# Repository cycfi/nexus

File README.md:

# Nexus
The Nexus is a small, flexible, and hacker friendly breakout box that connects your multichannel guitar to the outside world using a specialized (LEMO compatible) multi-pin connector for up to 15 channels of audio and 7 channels of analog control voltages for by-wire (remote) control of volume, tone, patch or effects. Audio may come from standard mono-pickups or from the Nu multichannel pickup. Analog control voltages are converted to MIDI control messages.

Refer to this repository to get the Eagle libraries used in our schematic and pcb files: https://github.com/cycfi/eagle_common

Hardware design files licensed under a [Creative Commons Attribution-ShareAlike 4.0 International License](https://creativecommons.org/licenses/by-sa/4.0/).

Software source code distributed under the [MIT License](https://opensource.org/licenses/MIT).

http://www.cycfi.com/

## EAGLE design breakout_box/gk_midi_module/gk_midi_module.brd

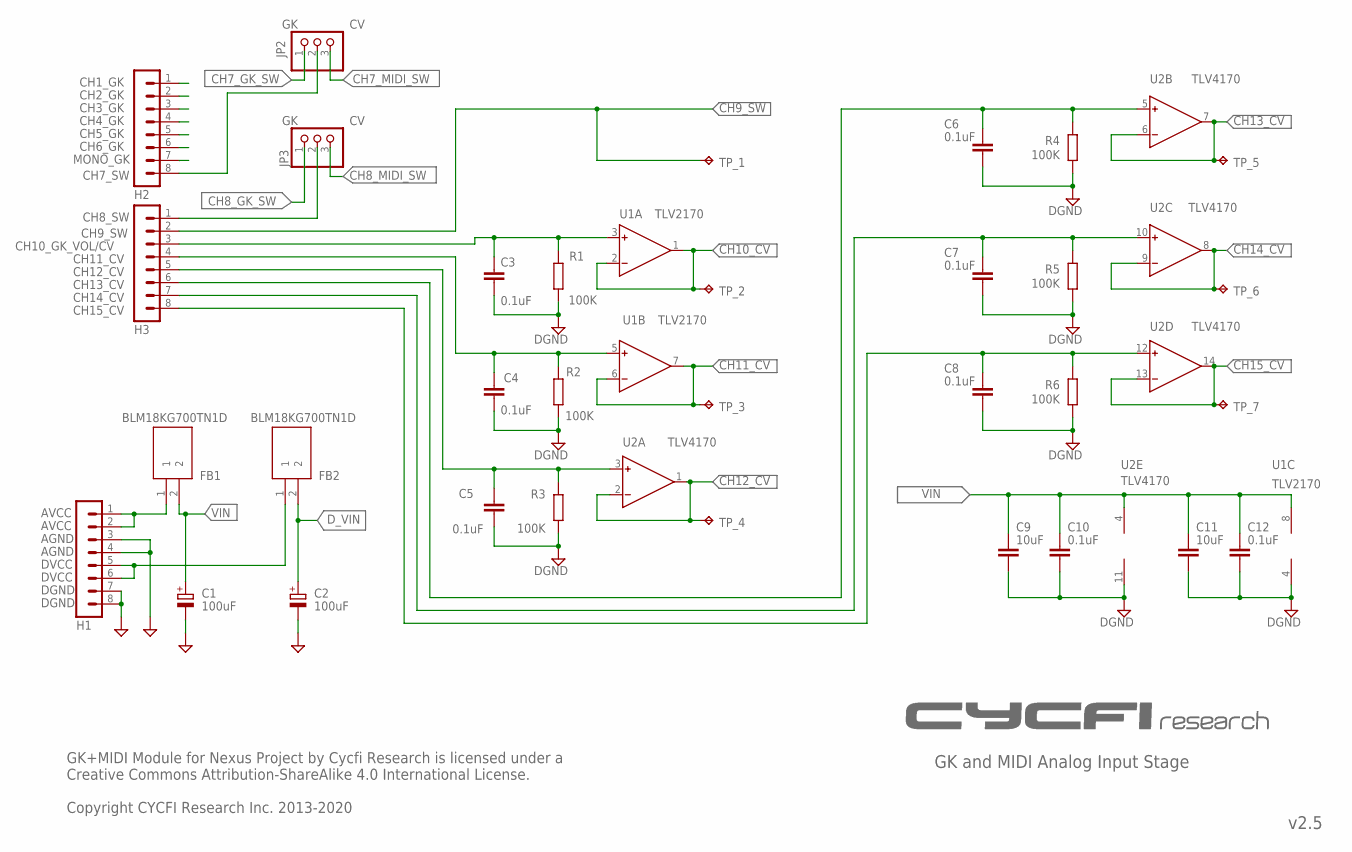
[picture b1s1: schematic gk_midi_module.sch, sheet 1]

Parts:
C1, C2: 100uF; 153CLV-0505
C3, C4, C5, C6, C7, C8, C10, C12: 0.1uF; C0603
C9, C11: 10uF; C0805
FB1: BLM18KG700TN1D; BEADC1608X75N
FB2: BLM18KG700TN1D; BEADC1608X75N; MANUFACTURER_PART_NUMBER BLM18KG700TN1D; MOUSER_PART_NUMBER 81-BLM18KG700TN1D
H1, H2, H3: MA08-1
JP2, JP3: PINHD-1X03_2.00; 1X03M
R1, R2, R3, R4, R5, R6: 100K; R0402
TP_1, TP_2, TP_3, TP_4, TP_5, TP_6, TP_7: TPB1,27; B1,27
U1: TLV2170DGKT; MSOP8
U2: LMV324; SSOP-14

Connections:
AVCC: FB1.1, H1.1, H1.2
CH1_GK: H2.1; also elsewhere on the board
CH2_GK: H2.2; also elsewhere on the board
CH3_GK: H2.3; also elsewhere on the board
CH4_GK: H2.4; also elsewhere on the board
CH5_GK: H2.5; also elsewhere on the board
CH6_GK: H2.6; also elsewhere on the board
CH7_GK_SW: JP2.1; also elsewhere on the board
CH7_GK_SW/CV: H2.8, JP2.2
CH7_MIDI_SW: JP2.3; also elsewhere on the board
CH8_GK_SW: JP3.1; also elsewhere on the board
CH8_GK_SW/CV: H3.1, JP3.2
CH8_MIDI_SW: JP3.3; also elsewhere on the board
CH9_SW: H3.2, TP_1.TP; also elsewhere on the board
CH10_CV: TP_2.TP, U1.1 (OUT), U1.2 (IN-); also elsewhere on the board
CH10_GK_VOL: C3.1, H3.3, R1.2, U1.3 (IN+); also elsewhere on the board
CH11_CV: TP_3.TP, U1.6 (IN-), U1.7 (OUT); also elsewhere on the board
CH12_CV: TP_4.TP, U2.1 (OUT), U2.2 (IN-); also elsewhere on the board
CH13_CV: TP_5.TP, U2.6 (IN-), U2.7 (OUT); also elsewhere on the board
CH14_CV: TP_6.TP, U2.8 (OUT), U2.9 (IN-); also elsewhere on the board
CH15_CV: TP_7.TP, U2.13 (IN-), U2.14 (OUT); also elsewhere on the board
CH15_CV_IN: C8.1, H3.8, R6.2, U2.12 (IN+)
DVCC: FB2.1, H1.5, H1.6
D_VIN: C2.+, FB2.2; also elsewhere on the board
GND: C1.-, C2.-, C3.2, C4.2, C5.2, C6.2, C7.2, C8.2, C9.2, C10.2, C11.2, C12.2, H1.3, H1.4, H1.7, H1.8, R1.1, R2.1, R3.1, R4.1, R5.1, R6.1, U1.4 (V-), U2.11 (V-); also elsewhere on the board
MONO_GK: H2.7; also elsewhere on the board
unnamed: C4.1, H3.4, R2.2, U1.5 (IN+)
unnamed: C5.1, H3.5, R3.2, U2.3 (IN+)
unnamed: C6.1, H3.6, R4.2, U2.5 (IN+)
unnamed: C7.1, H3.7, R5.2, U2.10 (IN+)
VIN: C1.+, C9.1, C10.1, C11.1, C12.1, FB1.2, U1.8 (V+), U2.4 (V+)

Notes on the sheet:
GK and MIDI Analog Input Stage
v2.5
CH9_SW
CH10_GK_VOL/CV
CH11_CV
CH12_CV
CH13_CV
CH14_CV
CH15_CV
DGND
AGND
GK+MIDI Module for Nexus Project by Cycfi Research is licensed under a Creative Commons Attribution-ShareAlike 4.0 International License. Copyright CYCFI Research Inc. 2013-2020
TLV4170
CH1_GK
CH2_GK
CH3_GK
CH4_GK
CH5_GK
CH6_GK
CH7_SW
MONO_GK
CH8_SW
U1C
U1B
U1A
TLV2170
U2A
U2B
U2C
U2D
U2E

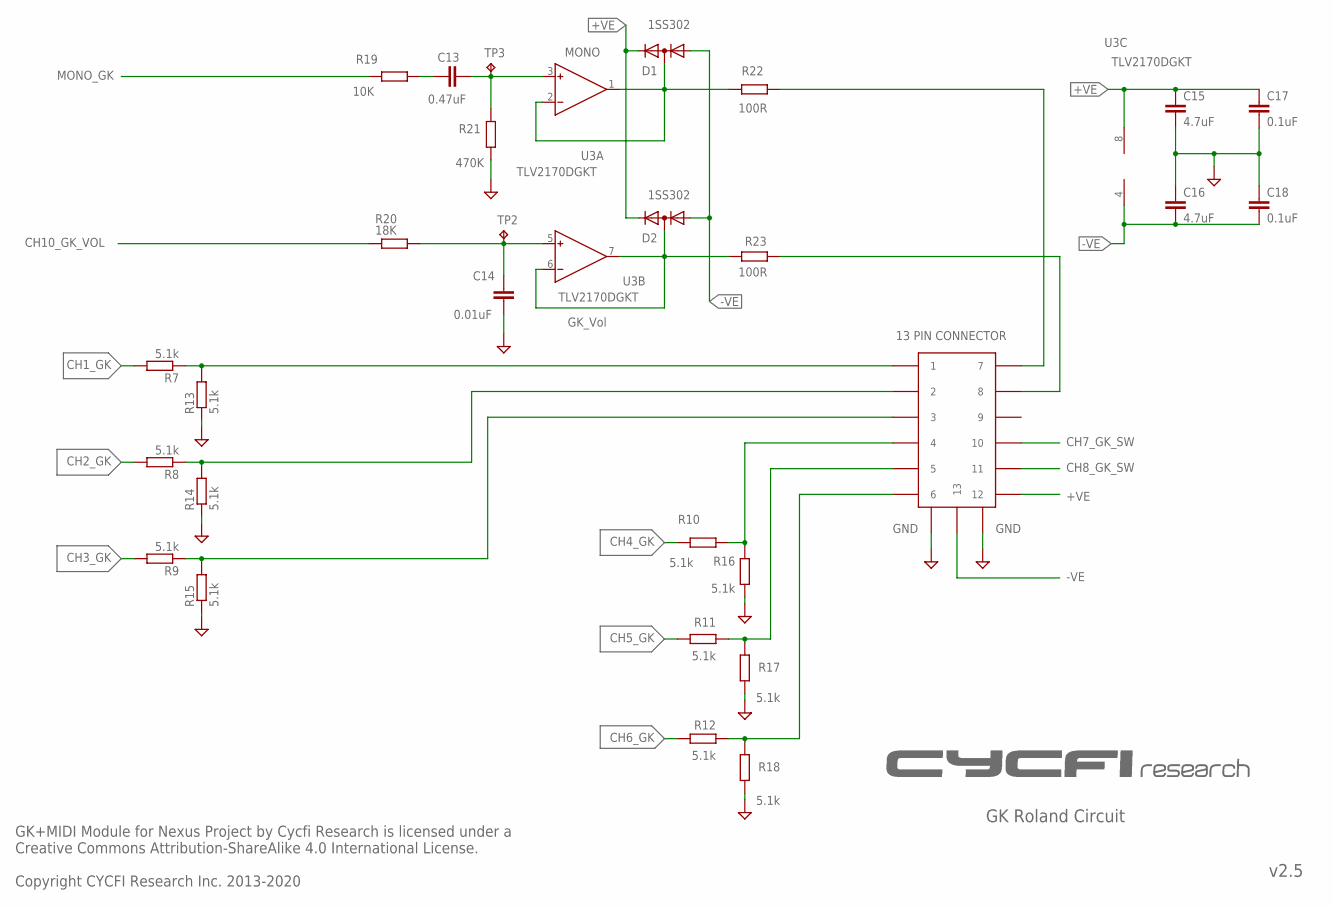
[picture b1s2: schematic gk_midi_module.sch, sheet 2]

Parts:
C13: 0.47uF; C0603
C14: 0.01uF; C0402
C15, C16: 4.7uF; C0603
C17, C18: 0.1uF; C0603
D1, D2: 1SS302; SC70-3
R7, R8, R9, R10, R11, R12, R13, R14, R15, R16, R17, R18: 5.1k; R0402
R19: 10K; R0402
R20: 18K; R0402
R21: 470K; R0402
R22, R23: 100R; R0603
TP2, TP3: TPB1,27; B1,27
U3: TLV2170DGKT; MSOP8
U$1: 13P_MIDI_2; 13P-MIDI-2

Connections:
+VE: C15.1, C17.1, D1.2 (K), D2.2 (K), U3.8 (V+), U$1.12
-VE: C16.2, C18.2, D1.1 (A), D2.1 (A), U3.4 (V-), U$1.13
CH1_GK: R7.2; also elsewhere on the board
CH2_GK: R8.2; also elsewhere on the board
CH3_GK: R9.2; also elsewhere on the board
CH4_GK: R10.2; also elsewhere on the board
CH5_GK: R11.2; also elsewhere on the board
CH6_GK: R12.2; also elsewhere on the board
CH7_GK_SW: U$1.10; also elsewhere on the board
CH8_GK_SW: U$1.11; also elsewhere on the board
CH10_GK_VOL: R20.1; also elsewhere on the board
GK_VOL: R23.2, U$1.8
GND: C14.2, C15.2, C16.1, C17.2, C18.1, R13.1, R14.1, R15.1, R16.1, R17.1, R18.1, R21.2, U$1.P$1 (14), U$1.P$2 (15); also elsewhere on the board
MONO_GK: R19.1; also elsewhere on the board
unnamed: R22.1, U$1.7
unnamed: D2.3 (AK), R23.1, U3.6 (IN-), U3.7 (OUT)
unnamed: C14.1, R20.2, TP2.TP, U3.5 (IN+)
unnamed: C13.2, R19.2
unnamed: C13.1, R21.1, TP3.TP, U3.3 (IN+)
unnamed: D1.3 (AK), R22.2, U3.1 (OUT), U3.2 (IN-)
unnamed: R7.1, R13.2, U$1.1
unnamed: R8.1, R14.2, U$1.2
unnamed: R9.1, R15.2, U$1.3
unnamed: R10.1, R16.2, U$1.4
unnamed: R11.1, R17.2, U$1.5
unnamed: R12.1, R18.2, U$1.6

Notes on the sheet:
GK Roland Circuit
MONO
GK_Vol
v2.5
GK+MIDI Module for Nexus Project by Cycfi Research is licensed under a Creative Commons Attribution-ShareAlike 4.0 International License. Copyright CYCFI Research Inc. 2013-2020
U3A
U3B
U3C
13 PIN CONNECTOR

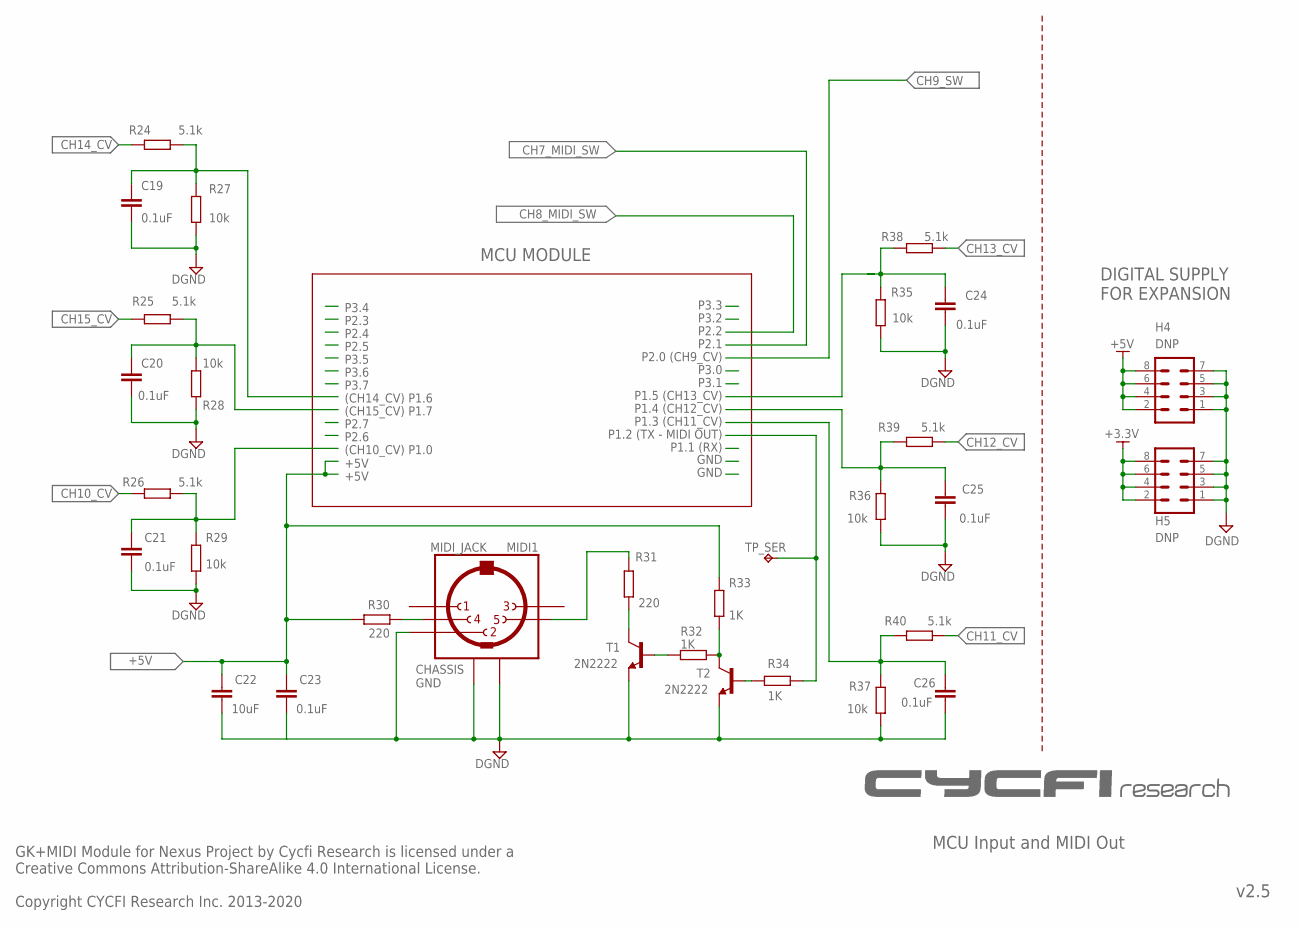
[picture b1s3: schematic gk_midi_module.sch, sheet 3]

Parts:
C19, C20, C21, C23, C24, C25, C26: 0.1uF; C0603
C22: 10uF; C0805
H4, H5: DNP; MA04-2
MIDI1: MIDI_JACK
R24, R25, R26, R38, R39, R40: 5.1k; R0402
R27, R28, R29, R35, R36, R37: 10k; R0402
R30, R31: 220; R0603
R32, R33, R34: 1K; R0402
T1, T2: 2N2222; SOT23-3
TP_SER: TPB1,27; B1,27

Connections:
+3.3V: H5.2, H5.4, H5.6, H5.8; also elsewhere on the board
+5V: C22.1, C23.1, H4.2, H4.4, H4.6, H4.8, R30.1, R33.2; also elsewhere on the board
CH10_CV: R26.1; also elsewhere on the board
CH11_CV: R40.2; also elsewhere on the board
CH12_CV: R39.2; also elsewhere on the board
CH13_CV: R38.2; also elsewhere on the board
CH14_CV: R24.1; also elsewhere on the board
CH15_CV: R25.1; also elsewhere on the board
GND: C19.2, C20.2, C21.2, C22.2, C23.2, C24.2, C25.2, C26.2, H4.1, H4.3, H4.5, H4.7, H5.1, H5.3, H5.5, H5.7, MIDI1.2, MIDI1.G1, MIDI1.G2, R27.2, R28.2, R29.2, R35.2, R36.2, R37.2, T1.2 (E), T2.2 (E); also elsewhere on the board
unnamed: MIDI1.5, R31.2
unnamed: R31.1, T1.3 (C)
unnamed: R32.2, T1.1 (B)
unnamed: MIDI1.4, R30.2
unnamed: R34.2, T2.1 (B)
unnamed: R32.1, R33.1, T2.3 (C)
P1.0: C21.1, R26.2, R29.1; also elsewhere on the board
P1.2: R34.1, TP_SER.TP; also elsewhere on the board
P1.3: C26.1, R37.1, R40.1; also elsewhere on the board
P1.4: C25.1, R36.1, R39.1; also elsewhere on the board
P1.5: C24.1, R35.1, R38.1; also elsewhere on the board
P1.6: C19.1, R24.2, R27.1; also elsewhere on the board
P1.7: C20.1, R25.2, R28.1; also elsewhere on the board

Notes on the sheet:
MCU Input and MIDI Out
v2.5
P3.3
P3.2
P2.2
P2.1
P2.0 (CH9_CV)
P3.0
P3.1
P1.5 (CH13_CV)
P1.4 (CH12_CV)
P1.3 (CH11_CV)
P1.2 (TX - MIDI OUT)
P1.1 (RX)
P3.4
P2.3
P2.4
P2.5
P3.5
P3.6
P3.7
(CH14_CV) P1.6
(CH15_CV) P1.7
P2.7
P2.6
(CH10_CV) P1.0
MCU MODULE
CHASSIS GND
DIGITAL SUPPLY FOR EXPANSION
GK+MIDI Module for Nexus Project by Cycfi Research is licensed under a Creative Commons Attribution-ShareAlike 4.0 International License. Copyright CYCFI Research Inc. 2013-2020

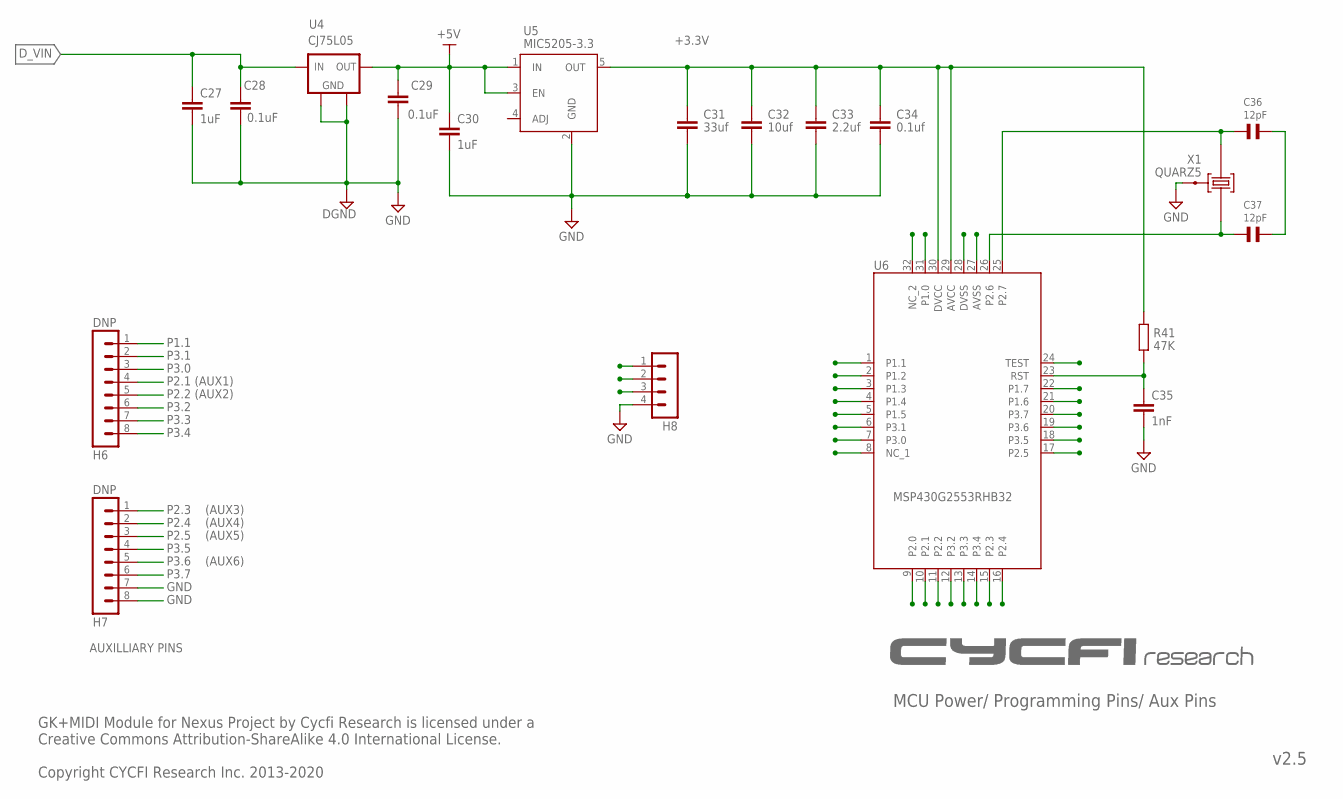
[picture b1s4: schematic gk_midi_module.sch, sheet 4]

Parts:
C27, C30: 1uF; C0402
C28, C29: 0.1uF; C0603
C31: 33uf; C0805
C32: 10uf; C0805
C33: 2.2uf; C0805
C34: 0.1uf; C0603
C35: 1nF; C0402
C36, C37: 12pF; 0603
H6, H7: DNP; MA08-1
H8: MA04-1
R41: 47K; R0402
U4: L78LXX; SOT89
U5: MIC5205-3.3; SOT23-5
U6: MSP430G2553RHB32; QFN32
X1: QUARZ5

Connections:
!RST: C35.1, H8.2, R41.2, U6.23 (RST)
+3.3V: C31.1, C32.1, C33.1, C34.1, H8.3, R41.1, U5.5 (OUT), U6.29 (AVCC), U6.30 (DVCC); also elsewhere on the board
+5V: C29.1, C30.1, U4.1 (IN), U5.1 (IN), U5.3 (EN); also elsewhere on the board
CH7_MIDI_SW: H6.4, U6.10 (P2.1); also elsewhere on the board
CH8_MIDI_SW: H6.5, U6.11 (P2.2); also elsewhere on the board
CH9_SW: U6.9 (P2.0); also elsewhere on the board
D_VIN: C27.1, C28.1, U4.3 (OUT); also elsewhere on the board
GND: C27.2, C28.2, C29.2, C30.2, C31.2, C32.2, C33.2, C34.2, C35.2, C36.1, C37.1, H7.7, H7.8, H8.4, U4.2 (GND), U4.2@1 (GND1), U5.2 (GND), U6.27 (AVSS), U6.28 (DVSS), X1.GND@0 (0); also elsewhere on the board
NC: U6.8 (NC_1)
P1.0: U6.31 (P1.0); also elsewhere on the board
P1.1: H6.1, U6.1 (P1.1)
P1.2: U6.2 (P1.2); also elsewhere on the board
P1.3: U6.3 (P1.3); also elsewhere on the board
P1.4: U6.4 (P1.4); also elsewhere on the board
P1.5: U6.5 (P1.5); also elsewhere on the board
P1.6: U6.21 (P1.6); also elsewhere on the board
P1.7: U6.22 (P1.7); also elsewhere on the board
P2.3: H7.1, U6.15 (P2.3)
P2.4: H7.2, U6.16 (P2.4)
P2.5: H7.3, U6.17 (P2.5)
P2.6: C37.2, U6.26 (P2.6), X1.1
P2.7: C36.2, U6.25 (P2.7), X1.2
P3.0: H6.3, U6.7 (P3.0)
P3.1: H6.2, U6.6 (P3.1)
P3.2: H6.6, U6.12 (P3.2)
P3.3: H6.7, U6.13 (P3.3)
P3.4: H6.8, U6.14 (P3.4)
P3.5: H7.4, U6.18 (P3.5)
P3.6: H7.5, U6.19 (P3.6)
P3.7: H7.6, U6.20 (P3.7)
TEST: H8.1, U6.24 (TEST)

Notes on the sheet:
MCU Power/ Programming Pins/ Aux Pins
v2.5
GK+MIDI Module for Nexus Project by Cycfi Research is licensed under a Creative Commons Attribution-ShareAlike 4.0 International License. Copyright CYCFI Research Inc. 2013-2020
CJ75L05
AUXILLIARY PINS
P2.1 (AUX1)
P2.2 (AUX2)
(AUX3)
(AUX4)
(AUX5)
(AUX6)

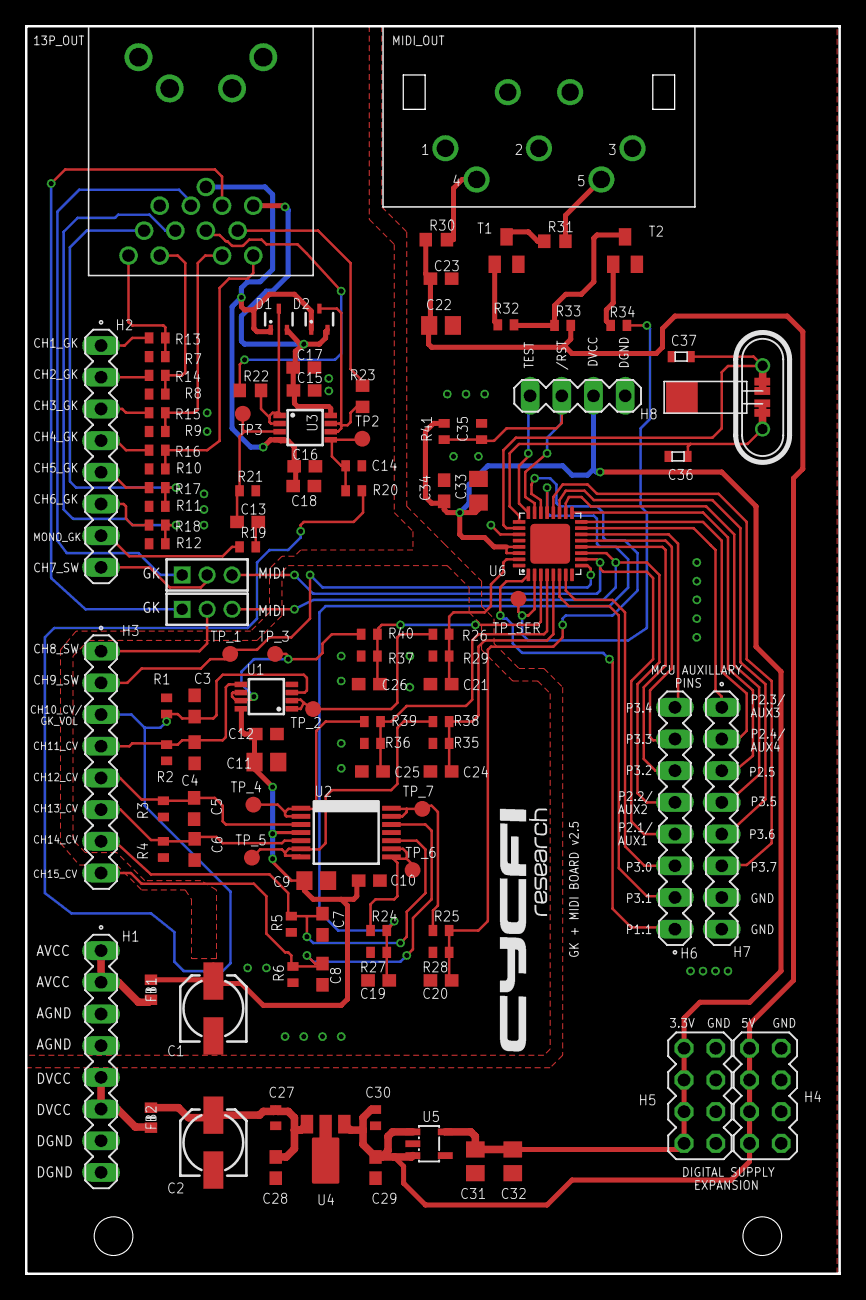
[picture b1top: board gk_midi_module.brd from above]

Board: 2 copper layers, 65.2 x 100.0 mm, 113 parts (0 on the bottom side), 77 nets.

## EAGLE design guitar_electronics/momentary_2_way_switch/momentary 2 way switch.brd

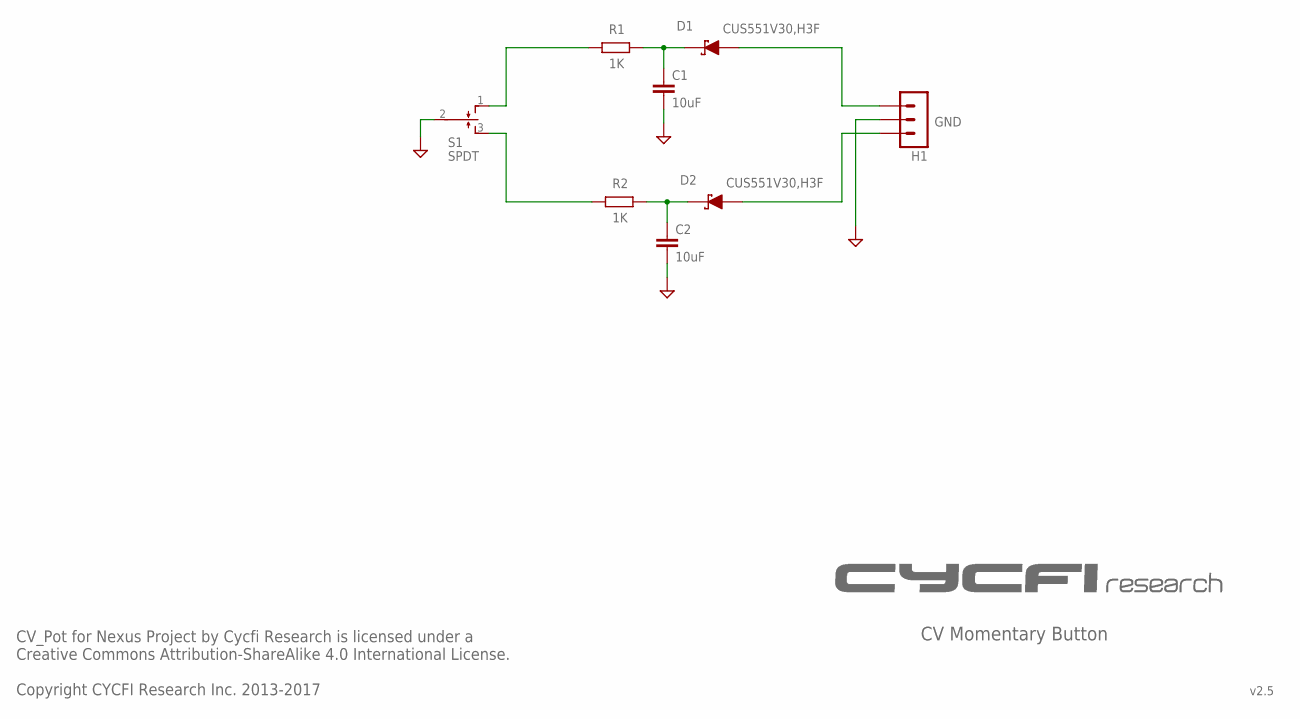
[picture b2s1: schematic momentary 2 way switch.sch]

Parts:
C1, C2: 10uF; C0603
D1, D2: CUS551V30,H3F; SOD-323
H1: 3PIN-SMD-2.54MM; 3P-SMD-2.54MM
R1, R2: 1K; R0402
S1: SPDT

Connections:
GND: C1.2, C2.2, H1.P$2 (2), S1.2
unnamed: C1.1, D1.2 (C), R1.2
unnamed: R1.1, S1.1 (O)
unnamed: C2.1, D2.2 (C), R2.2
unnamed: R2.1, S1.3 (S)
SW1: D2.1 (A), H1.P$3 (3)
SW2: D1.1 (A), H1.P$1 (1)

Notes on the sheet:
CV_Pot for Nexus Project by Cycfi Research is licensed under a Creative Commons Attribution-ShareAlike 4.0 International License. Copyright CYCFI Research Inc. 2013-2017
v2.5
CV Momentary Button
GND

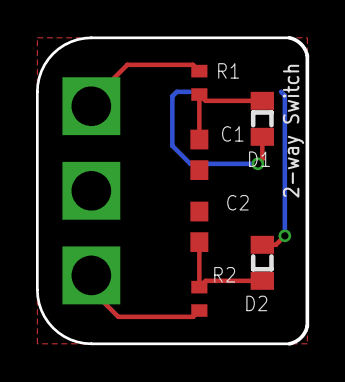
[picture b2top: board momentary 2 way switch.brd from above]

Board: 2 copper layers, 15.0 x 17.0 mm, 8 parts (1 on the bottom side), 7 nets.

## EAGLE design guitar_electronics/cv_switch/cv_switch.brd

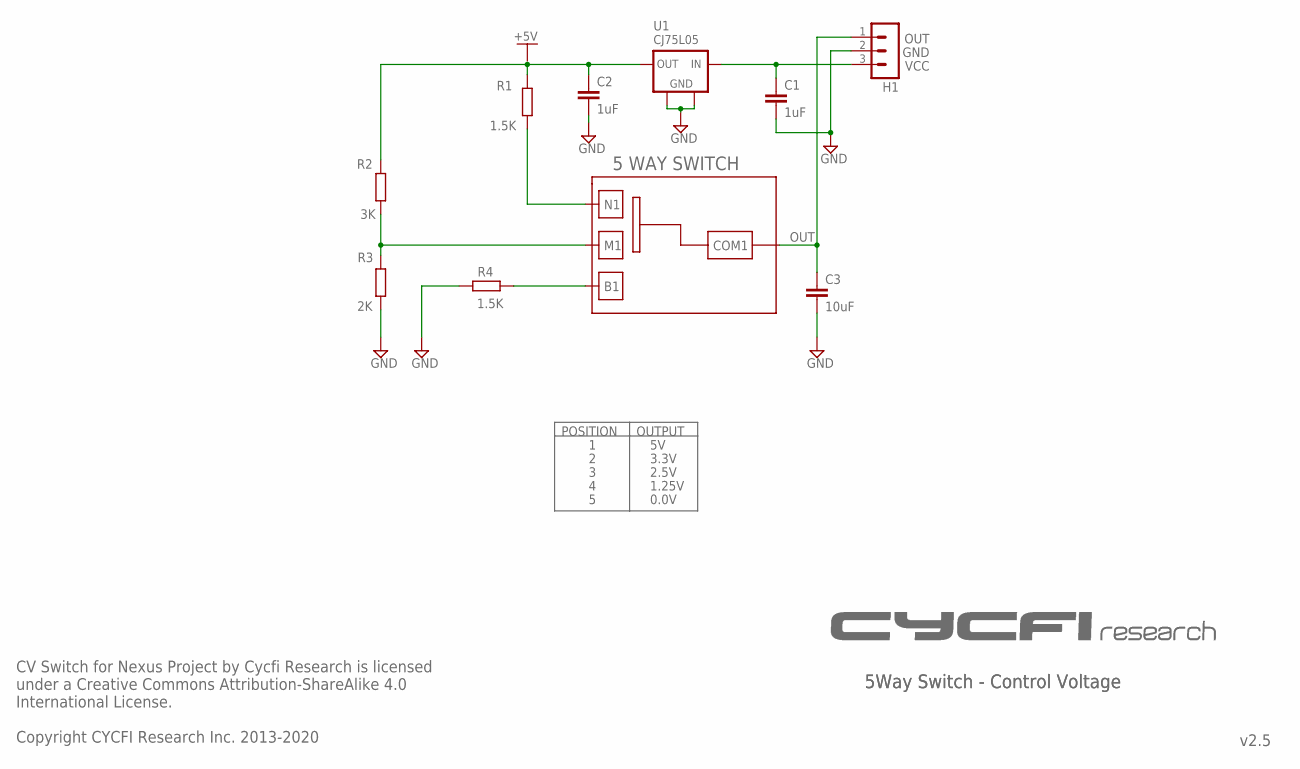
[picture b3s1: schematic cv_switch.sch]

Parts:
C1, C2: 1uF; C0603
C3: 10uF; C0603
H1: MA03-1_EDITED; MA03-1_
R1, R4: 1.5K; R0402
R2: 3K; R0402
R3: 2K; R0402
U1: CJ75L05; SOT89
U$1: 5WAY_SW_1; 5WAY_SW_CASTELLATED

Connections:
+5V: C2.1, R1.2, R2.2, U1.1 (IN)
GND: C1.2, C2.2, C3.2, H1.2, R3.1, R4.1, U1.2 (GND), U1.2@1 (GND1)
unnamed: C1.1, H1.3, U1.3 (OUT)
unnamed: R4.2, U$1.B1
unnamed: R2.1, R3.2, U$1.M1
unnamed: R1.1, U$1.N1
OUT: C3.1, H1.1, U$1.COM1

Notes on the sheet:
VCC
GND
OUT
5Way Switch - Control Voltage
v2.5
CV Switch for Nexus Project by Cycfi Research is licensed under a Creative Commons Attribution-ShareAlike 4.0 International License. Copyright CYCFI Research Inc. 2013-2020
POSITION
OUTPUT
3.3V
2.5V
1.25V
0.0V
CJ75L05

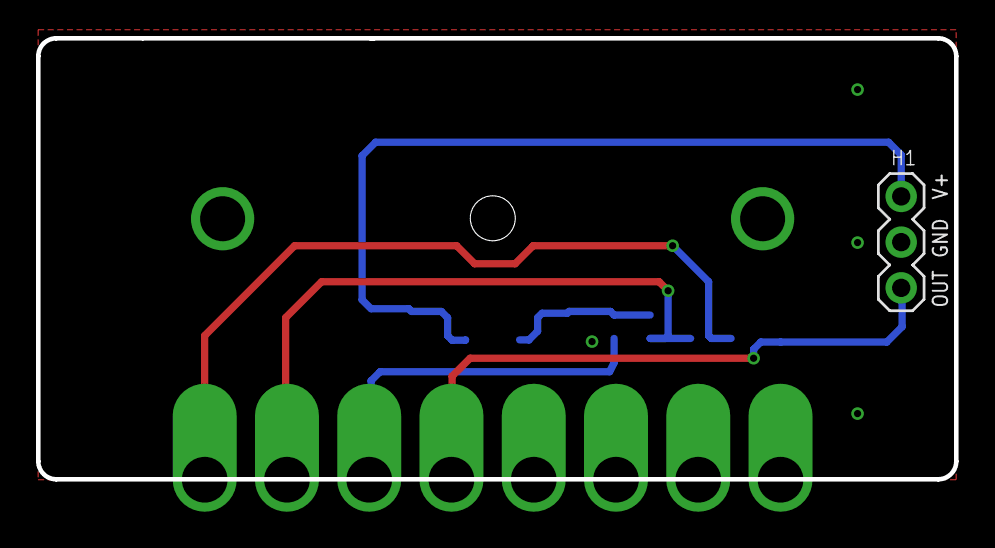
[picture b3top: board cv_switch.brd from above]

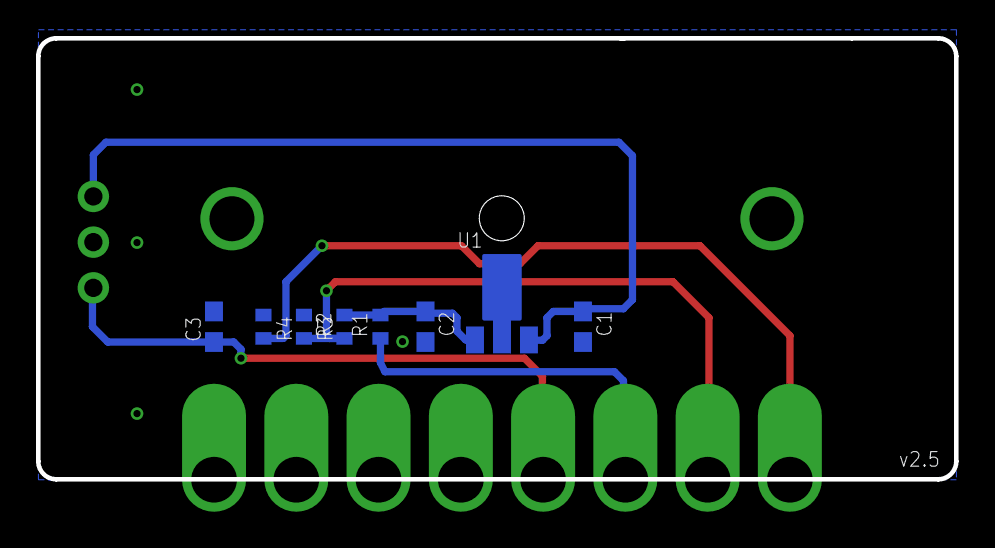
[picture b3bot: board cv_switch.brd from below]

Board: 2 copper layers, 51.0 x 24.5 mm, 10 parts (8 on the bottom side), 7 nets.

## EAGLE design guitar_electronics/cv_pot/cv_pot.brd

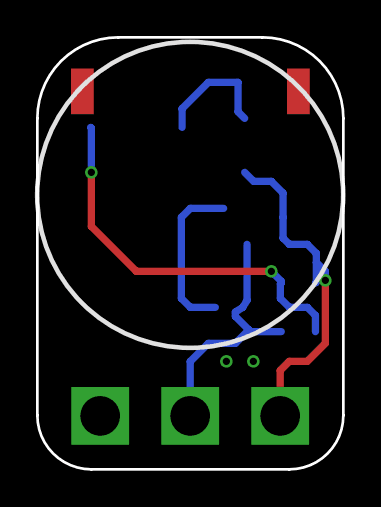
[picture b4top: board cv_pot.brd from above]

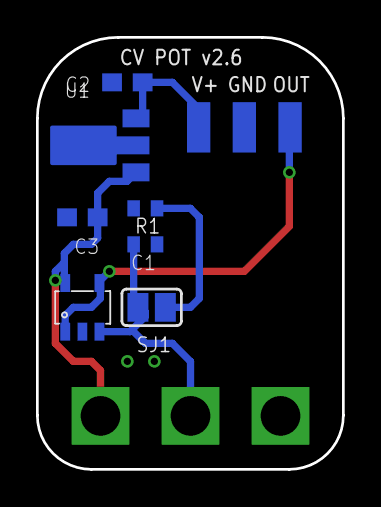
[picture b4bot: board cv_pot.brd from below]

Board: 2 copper layers, 17.0 x 24.0 mm, 11 parts (8 on the bottom side), 6 nets.

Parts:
C1: 0.1uF; C0402
C2, C3: 1uF; C0603
GND1, GND2: SMD1,27-2,54
H1: 3PIN-SMD-2.54MM; 3P-SMD-2.54MM
POT1: 25K; POT_EU_PDB181GTR
R1: R0402
SJ1: SJ
U1: L78LXX; SOT89
U2: TLV6001; SOT23-5

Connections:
GND: C1.2, C2.1, C3.1, GND1.1, GND2.1, H1.P$2, POT1.A1, R1.1, U1.2, U1.2@1, U2.2
unnamed: C2.2, H1.P$3, U1.3
unnamed: C3.2, POT1.A3, U1.1, U2.5
unnamed: C1.1, POT1.A2, SJ1.2, U2.3
unnamed: R1.2, SJ1.1
unnamed: H1.P$1, U2.1, U2.4

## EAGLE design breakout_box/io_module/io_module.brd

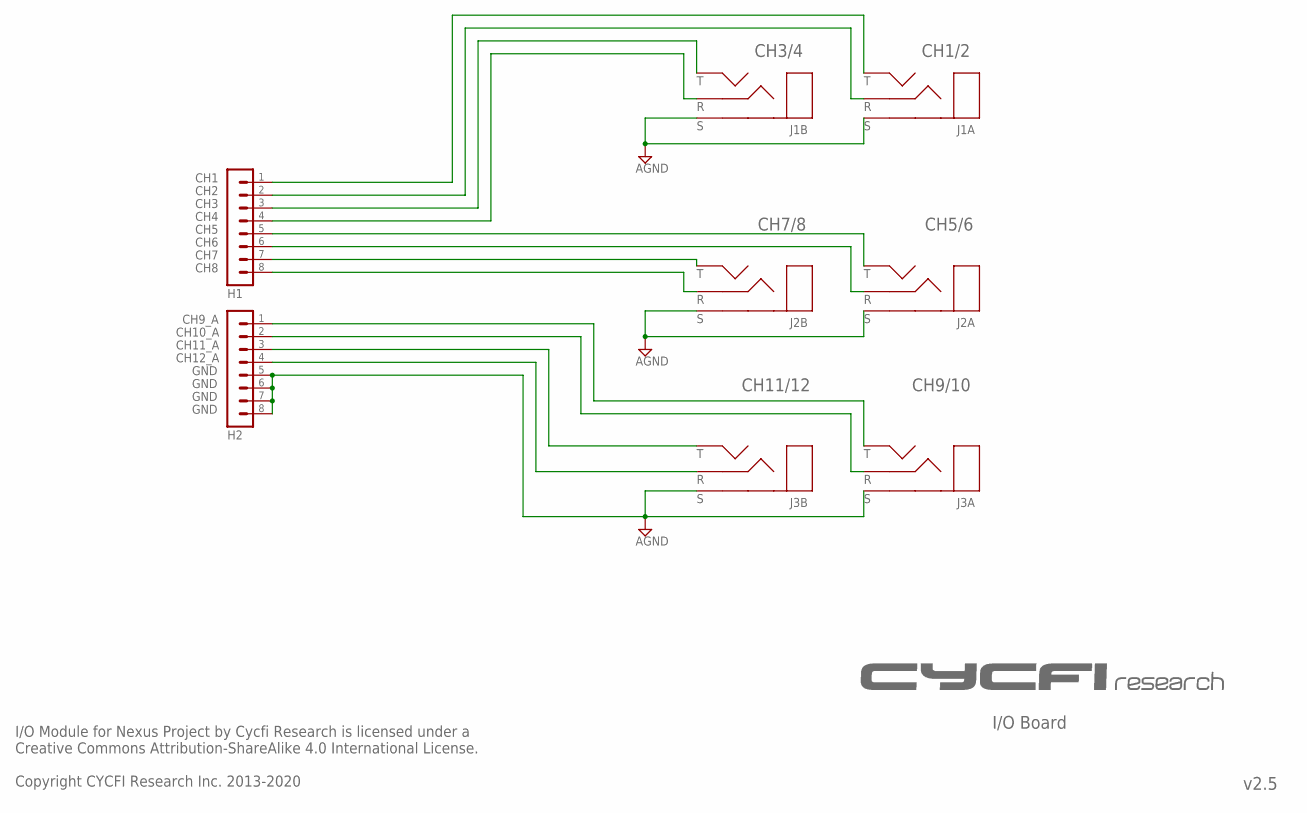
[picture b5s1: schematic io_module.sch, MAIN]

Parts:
H1, H2: MA08-1
J1, J2, J3: ZHEJINAG_CK_STSJACKS; ZHEJINAG_CK_6.35

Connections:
GND: H2.5, H2.6, H2.7, H2.8, J1.2S (S), J1.S, J2.2S (S), J2.S, J3.2S (S), J3.S
unnamed: H1.1, J1.2T (T)
unnamed: H1.3, J1.T
unnamed: H1.4, J1.R
unnamed: H1.5, J2.2T (T)
unnamed: H1.6, J2.2R (R)
unnamed: H1.7, J2.T
unnamed: H1.8, J2.R
unnamed: H2.1, J3.2T (T)
unnamed: H2.2, J3.2R (R)
unnamed: H2.3, J3.T
unnamed: H2.4, J3.R
unnamed: H1.2, J1.2R (R)

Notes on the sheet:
I/O Board
v2.5
I/O Module for Nexus Project by Cycfi Research is licensed under a Creative Commons Attribution-ShareAlike 4.0 International License. Copyright CYCFI Research Inc. 2013-2020
CH1
CH2
CH3
CH4
CH5
CH6
CH7
CH8
CH9_A
CH10_A
CH11_A
CH12_A
CH1/2
CH3/4
CH5/6
CH7/8
CH9/10
CH11/12
J1A
J1B
J2B
J2A
J3A
J3B

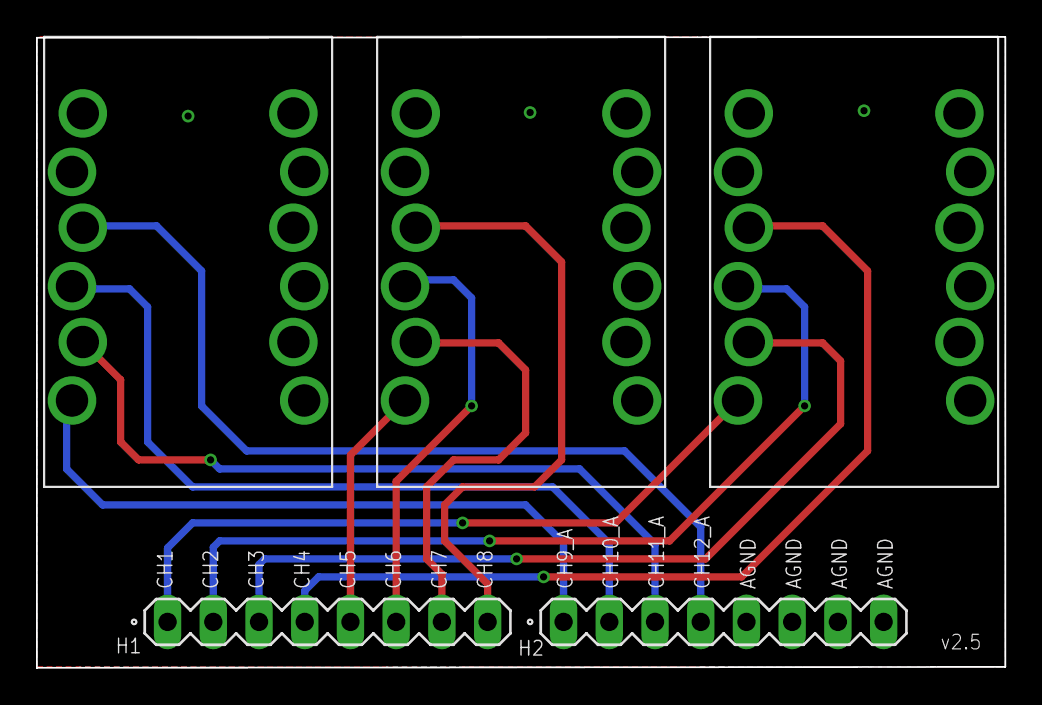
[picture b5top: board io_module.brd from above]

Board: 2 copper layers, 53.8 x 35.0 mm, 5 parts (0 on the bottom side), 13 nets.

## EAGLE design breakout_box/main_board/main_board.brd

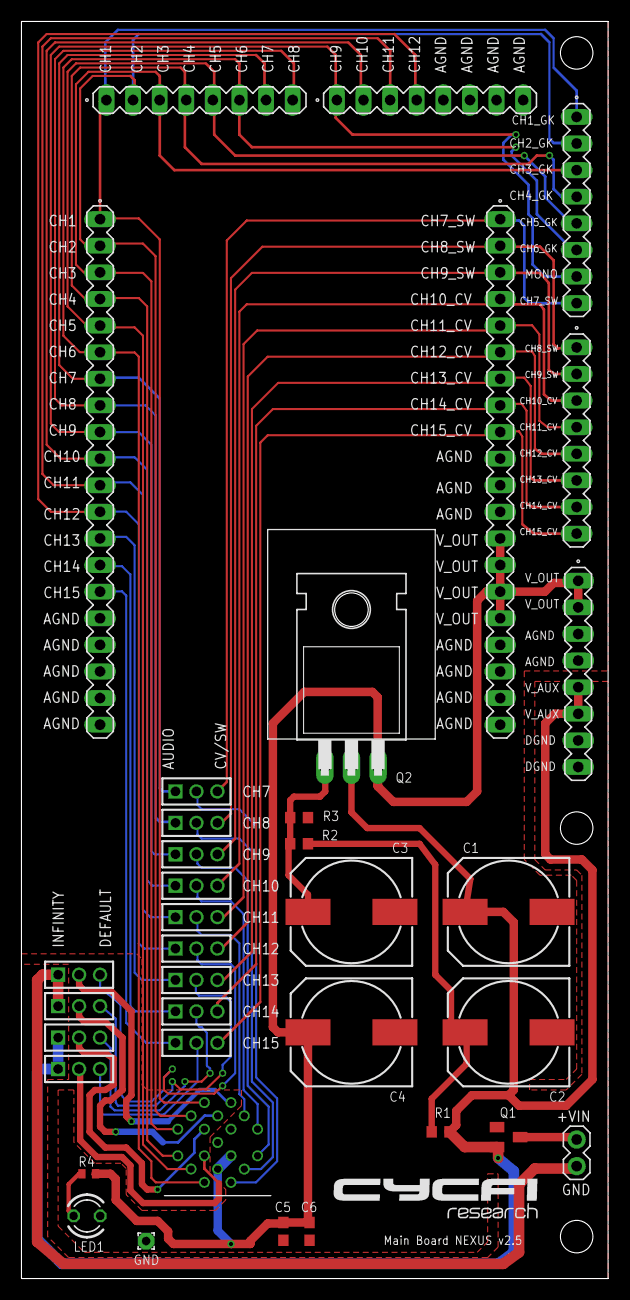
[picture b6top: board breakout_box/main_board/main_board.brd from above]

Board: 2 copper layers, 56.0 x 120.0 mm, 36 parts (0 on the bottom side), 44 nets.

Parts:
C1, C2, C3, C4: 470uF; 140CLH-1010
C5: 1uF; C0603
C6: 0.1uF; C0603
CN1: 19PIN_LEMO
GND: TH-PAD-1.6/0.8
H1, H2: DNP; MA20-1
H3, H4, H7, H8, H17: MA08-1
H6: MA02-1
JP1, JP2, JP3, JP4, JP5, JP6, JP7, JP8, JP9, JP10, JP11, JP12, JP13: 1X03M
LED1: LED3MM
Q1: DMP3099L; SOT23
Q2: TIP122; TO-220H
R1, R2: 220R; R0603
R3: 12k; R0603
R4: 4.7k; R0402

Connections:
GND: C1.-, C2.-, C3.-, C4.-, C5.2, C6.2, CN1.P$18, CN1.P$19, GND.1, H1.10, H1.11, H1.12, H1.17, H1.18, H1.19, H1.20, H2.16, H2.17, H2.18, H2.19, H2.20, H4.5, H4.6, H4.7, H4.8, H6.1, H8.3, H8.4, H8.7, H8.8, JP12.1, JP13.1, LED1.K, Q1.1, R3.1
unnamed: CN1.P$2, H2.2, H3.2, H17.2
unnamed: CN1.P$1, H2.1, H3.1, H17.1
unnamed: CN1.P$8, JP2.2
unnamed: H6.2, Q1.3
unnamed: H1.2, H7.1, JP2.3
unnamed: C3.+, Q2.1, R2.1, R3.2
unnamed: H1.1, H17.8, JP1.3
unnamed: C2.+, R1.1, R2.2
unnamed: CN1.P$5, H2.5, H3.5, H17.5
unnamed: JP9.2, JP10.3
unnamed: H2.7, H3.7, JP1.1
unnamed: CN1.P$7, JP1.2
unnamed: H1.3, H7.2, JP3.3
unnamed: CN1.P$10, JP4.2
unnamed: CN1.P$11, JP5.2
unnamed: CN1.P$12, JP13.2
unnamed: CN1.P$9, JP3.2
unnamed: H2.10, H4.2, JP4.1
unnamed: H2.13, JP7.1
unnamed: H2.14, JP8.1
unnamed: H2.15, JP9.1
unnamed: JP8.2, JP11.3
unnamed: LED1.A, R4.2
unnamed: H1.5, H7.4, JP5.3
unnamed: H1.4, H7.3, JP4.3
unnamed: H2.12, H4.4, JP6.1
unnamed: H2.11, H4.3, JP5.1
unnamed: H1.6, H7.5, JP6.3
unnamed: CN1.P$3, H2.3, H3.3, H17.3
unnamed: H2.9, H4.1, H17.7, JP3.1
unnamed: H1.7, H7.6, JP7.3
unnamed: H1.8, H7.7, JP8.3
unnamed: H1.9, H7.8, JP9.3
unnamed: CN1.P$13, JP12.2
unnamed: CN1.P$14, JP11.2
unnamed: CN1.P$15, JP10.2
unnamed: CN1.P$4, H2.4, H3.4, H17.4
unnamed: JP7.2, JP12.3
unnamed: CN1.P$6, H2.6, H3.6, H17.6
unnamed: H2.8, H3.8, JP2.1
unnamed: JP6.2, JP13.3
V_AUX: C1.+, H8.5, H8.6, JP10.1, JP11.1, Q1.2, Q2.2, R1.2
V_OUT: C4.+, C5.1, C6.1, CN1.P$16, CN1.P$17, H1.13, H1.14, H1.15, H1.16, H8.1, H8.2, Q2.3, R4.1

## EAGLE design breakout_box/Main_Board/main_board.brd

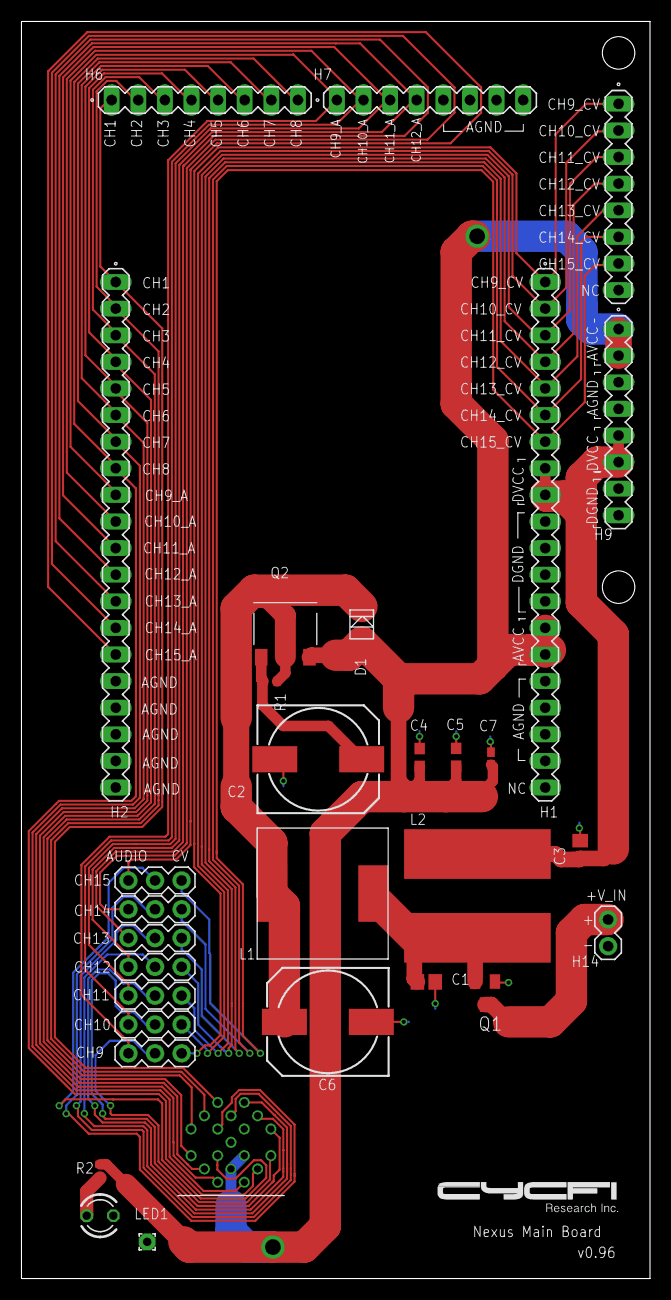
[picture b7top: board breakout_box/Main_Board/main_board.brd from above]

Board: 2 copper layers, 60.0 x 120.0 mm, 31 parts (0 on the bottom side), 37 nets.

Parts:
C1, C3: 22uF; C0805
C2: 470uF; 140CLH-1010
C4: 1uF; C0603
C5: 10uF; C0603
C6: 1000uF; 140CLH-1010
C7: 1nF; C0402K
CN1: 19PIN_LEMO
D1: FM4004W; SMX
GND: TH-PAD-1.6/0.8
H1, H2: MA20-1
H3, H4, H5, H10, H11, H12, H13: MA03-1_
H6, H7, H8, H9: MA08-1
H14: MA02-1
L1: 1mH; SDR
L2: 82uH; L1280
LED1: LED3MM
Q1: DMP3099L; SOT23
Q2: DSS6060; SOT-223-4
R1: 1k; R0402
R2: 4.7k; R0402

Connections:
+AVCC: C4.1, C5.1, C7.1, CN1.P$16, CN1.P$17, D1.ANODE, H1.14, H1.15, H9.1, H9.2, Q2.P$3, R2.1
+DVCC: C3.1, H1.8, H1.9, H9.5, H9.6, L1.P$2
GND: C1.2, C2.-, C3.2, C4.2, C5.2, C6.-, C7.2, CN1.P$18, CN1.P$19, GND.1, H1.10, H1.11, H1.12, H1.13, H1.16, H1.17, H1.18, H1.19, H2.16, H2.17, H2.18, H2.19, H2.20, H7.5, H7.6, H7.7, H7.8, H9.3, H9.4, H9.7, H9.8, H14.1, LED1.K, Q1.1
unnamed: H2.13, H3.1
unnamed: H14.2, Q1.3
unnamed: H2.14, H4.1
unnamed: CN1.P$1, H2.1, H6.1
unnamed: CN1.P$2, H2.2, H6.2
unnamed: CN1.P$3, H2.3, H6.3
unnamed: CN1.P$4, H2.4, H6.4
unnamed: CN1.P$5, H2.5, H6.5
unnamed: H1.1, H8.1, H10.3
unnamed: CN1.P$6, H2.6, H6.6
unnamed: CN1.P$7, H2.7, H6.7
unnamed: CN1.P$8, H2.8, H6.8
unnamed: CN1.P$9, H10.2
unnamed: CN1.P$10, H11.2
unnamed: CN1.P$11, H12.2
unnamed: CN1.P$12, H13.2
unnamed: H2.15, H5.1
unnamed: H2.10, H7.2, H11.1
unnamed: C1.1, L1.P$1, L2.P$1, Q1.2
unnamed: C2.+, Q2.P$1, R1.1
unnamed: C6.+, D1.CATHODE, L2.P$2, Q2.P$2, Q2.P$4, R1.2
unnamed: LED1.A, R2.2
unnamed: H1.3, H8.3, H12.3
unnamed: H1.2, H8.2, H11.3
unnamed: H2.12, H7.4, H13.1
unnamed: H2.11, H7.3, H12.1
unnamed: H1.4, H8.4, H13.3
unnamed: H2.9, H7.1, H10.1
unnamed: H1.5, H3.3, H8.5
unnamed: H1.6, H4.3, H8.6
unnamed: H1.7, H5.3, H8.7
unnamed: CN1.P$13, H3.2
unnamed: CN1.P$14, H4.2
unnamed: CN1.P$15, H5.2

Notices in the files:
parts and their libraries:
m-pad-2.1: License : GNU General Public License version 2 (see bottom)
